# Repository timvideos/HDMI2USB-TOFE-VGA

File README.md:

# VGA TOFE Expansion Board

This repository contains a TOFE board for VGA capture based on 
[Rohit's vmodvga board](https://github.com/timvideos/HDMI2USB-vmodvga).

For [more information on the TOFE interface, see the HDMI2USB website](http://hdmi2usb.tv/tofe).
For the [KiCad website](http://kicad.org/) for more information on using it.

## Parts

The RCA Jack is a little hard to find, but it can be found at the following
locations (it is also totally optional);

 * [Element14](http://au.element14.com/pro-signal/mr-100h/socket-phono-pcb/dp/1267381) - Order Code: 1267381

## License

The contents of this repository excluding "third_party" folder is released
under your choice of the following two licences:

 * the "Creative Commons Attribution-ShareAlike 4.0 International License" (CC
   BY-SA 4.0) full text of this license is included in the LICENSE file and a
   copy can also be found at http://creativecommons.org/licenses/by-sa/4.0/

 * the "TAPR Open Hardware License" full text of this license is included in
   the LICENSE file and a copy can also be found at http://www.tapr.org/OHL

Both these licenses are "share and share alike" licenses and require **any**
derivative work to also be released. Please read the license fully to make sure
you comply with all your obligations.  

## Authors

This board has been a joint effort from many people, some of the major
contributors are;

 * Phyllis McKeever <mccircuit@yahoo.com>
 * Tim 'mithro' Ansell <mithro@mithis.com>
 * Kenny Duffus <kenny@duffus.org>
 * Rohit Kumar Singh <rohit@gmx.it>
 * Jahanzeb Ahmad <jahanzeb1982@gmail.com>

----

Original documentation from vmodvga board.

## Documentation

 * [Project blog](https://dreamsxtrinsic.blogspot.com/) for weekly and daily updates
 * [vMod-VGA Code Block Diagram](https://docs.google.com/drawings/d/1-_QcqhuEnqGTb0JCZim7DaP1v0BfKb7fcv-28n1iaC0/edit?usp=sharing)
 * [Code structure explained in this document](https://docs.google.com/document/d/11dfCeLtNUrjcst97REtgqLIln-_pKwHgGT3xKjOamxs/edit?usp=sharing)
 * [vMod-VGA VHDCI Pin Usage](https://docs.google.com/spreadsheets/d/1f-rBfR98f_ZZNIB7GFV79CGSHQNpj47uOU0JDwOJnV8/edit?usp=sharing)
 * [AD9984A Register Settings](https://docs.google.com/spreadsheets/d/1GH8NDtB8ceGhJEVZQujcXdxDPSw_wLqhg_3s436kkSs/edit?usp=sharing) for easier register settings
 * [Code Test points](https://docs.google.com/spreadsheets/d/12sMpliuKs6eSY12Fc8JHHKd0Y-Cz1OmEMRZJ5Vne3Vg/edit?usp=sharing) I compiled during whole project during
 * [Autodetection guidelines](https://docs.google.com/document/d/1ZhDz50rve5UmnmyKynxySLHqfFuOwBPM7pYFoHo9uvs/edit?usp=sharing)
 * [I2C Tools & Debugging](https://docs.google.com/document/d/1rNem5J1_V4QUOei_MHRzZVJfjsTon8fnE3eTlhzsrj8/edit?usp=sharing)
 * [PCB v02 Requirements Doc](https://docs.google.com/document/d/1EVi7m_RxV2RLTFDjguj92tawxPkJdG1kjHW0T4Z_cDw/edit?usp=sharing)

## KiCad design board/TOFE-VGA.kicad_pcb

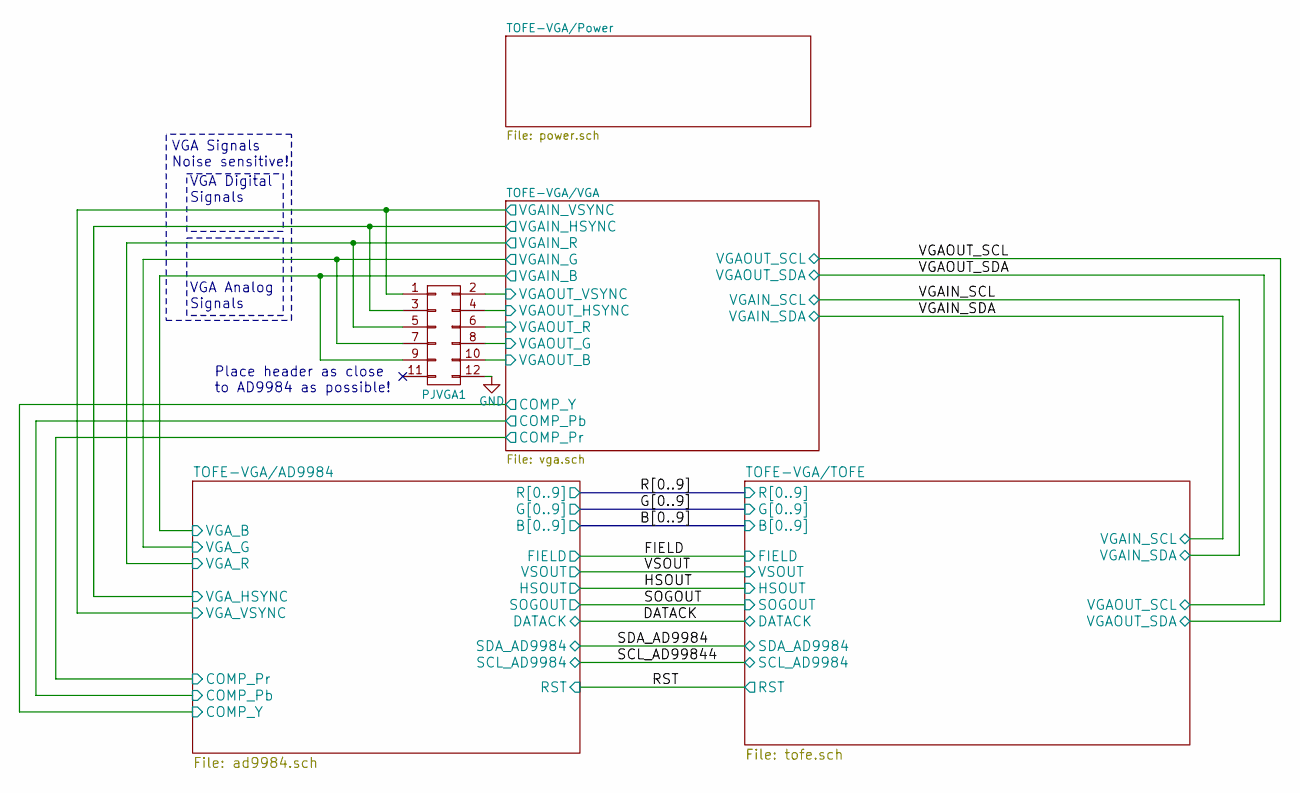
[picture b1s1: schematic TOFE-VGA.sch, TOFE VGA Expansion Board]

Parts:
PJVGA1: CONN_02X06; Pin_Header_Straight_2x06

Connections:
/TOFE-VGA/VGA/VGAIN_B: PJVGA1.9; also elsewhere on the board
/TOFE-VGA/VGA/VGAIN_G: PJVGA1.7; also elsewhere on the board
/TOFE-VGA/VGA/VGAIN_HSYNC: PJVGA1.3; also elsewhere on the board
/TOFE-VGA/VGA/VGAIN_R: PJVGA1.5; also elsewhere on the board
/TOFE-VGA/VGA/VGAIN_VSYNC: PJVGA1.1; also elsewhere on the board
/TOFE-VGA/VGA/VGAOUT_B: PJVGA1.10; also elsewhere on the board
/TOFE-VGA/VGA/VGAOUT_G: PJVGA1.8; also elsewhere on the board
/TOFE-VGA/VGA/VGAOUT_HSYNC: PJVGA1.4; also elsewhere on the board
/TOFE-VGA/VGA/VGAOUT_R: PJVGA1.6; also elsewhere on the board
/TOFE-VGA/VGA/VGAOUT_VSYNC: PJVGA1.2; also elsewhere on the board
GND: PJVGA1.12; also elsewhere on the board

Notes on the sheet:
VGA Signals Noise sensitive!
VGA Analog Signals
Place header as close to AD9984 as possible!
VGA Digital Signals

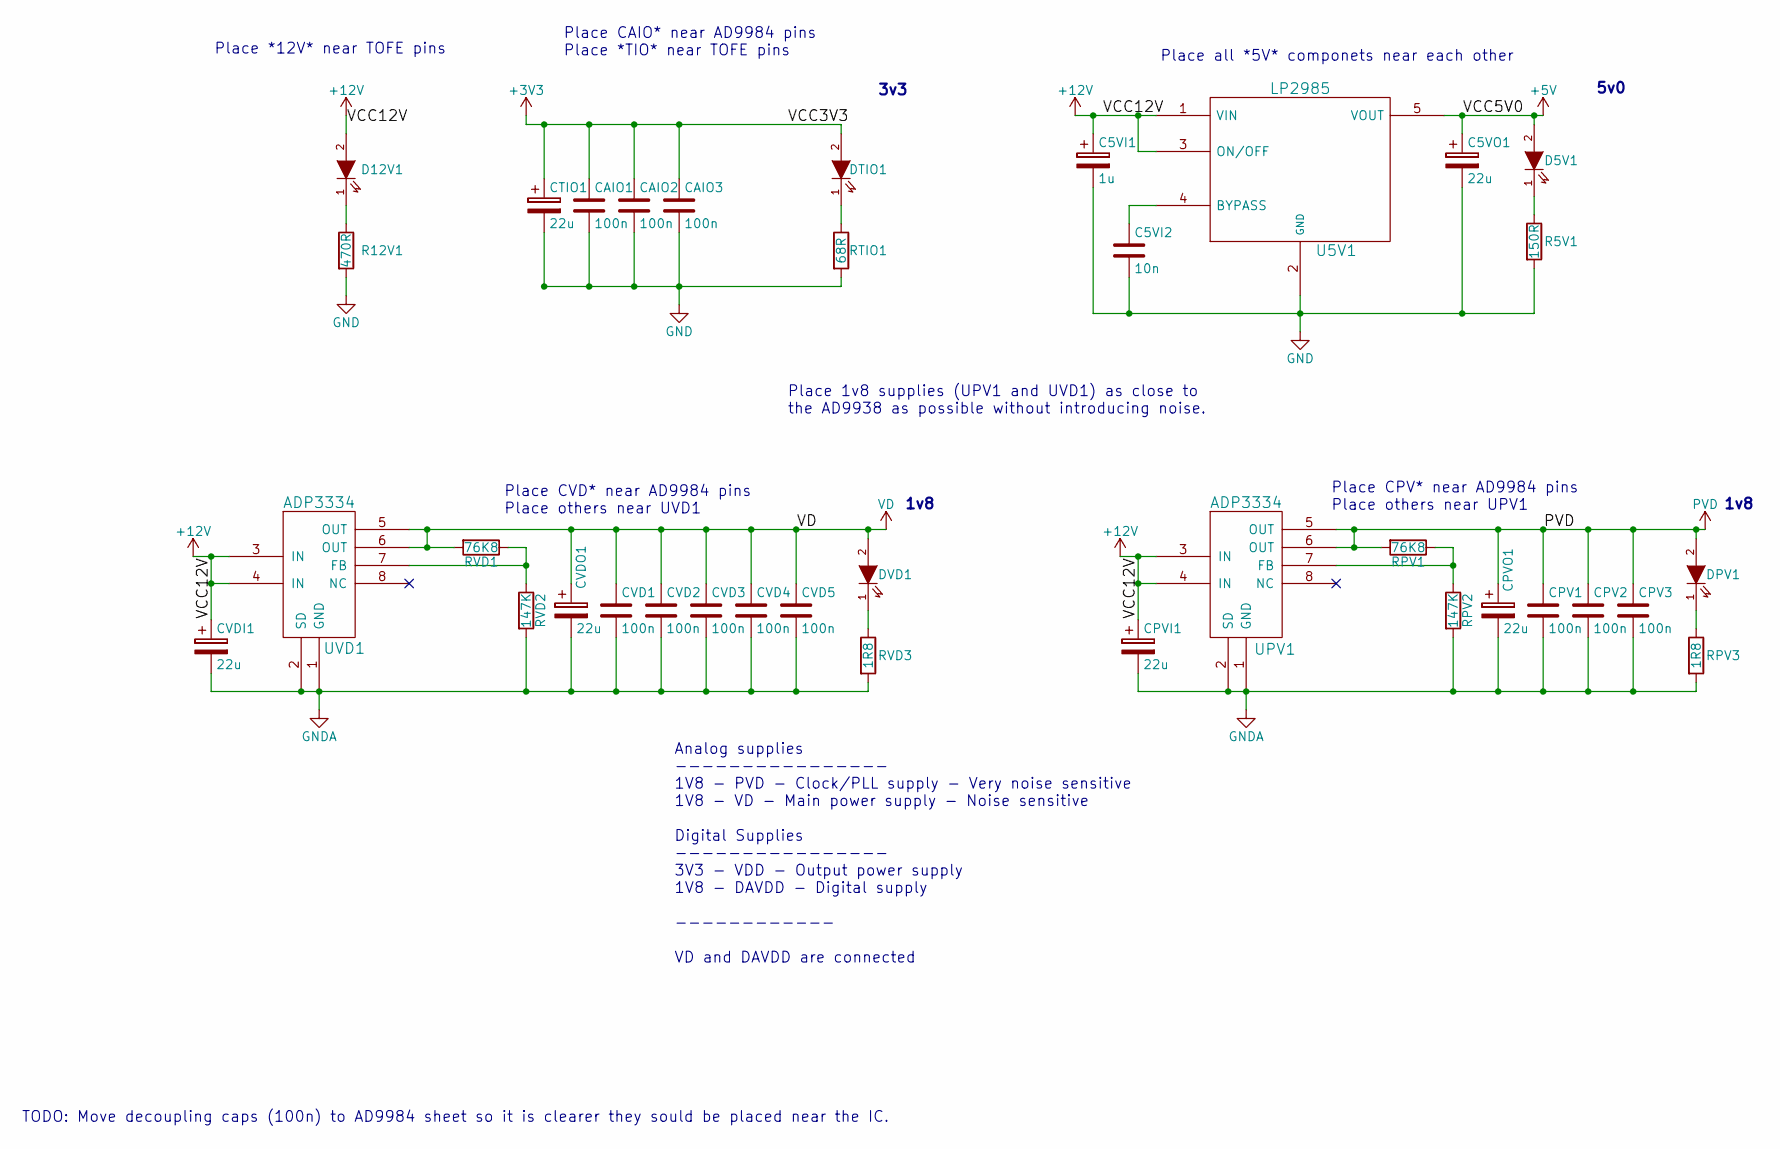
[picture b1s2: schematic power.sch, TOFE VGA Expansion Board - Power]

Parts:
C5VI1: 1u; c_elec_4x5.8
C5VI2: 10n; R_0805_HandSoldering
C5VO1: 22u; c_elec_4x5.8
CAIO1, CAIO2, CAIO3: 100n; R_0805_HandSoldering
CPV1, CPV2, CPV3: 100n; R_0805_HandSoldering
CPVI1: 22u; c_elec_4x5.8
CPVO1: 22u; c_elec_4x5.8
CTIO1: 22u; c_elec_4x5.8
CVD1, CVD2, CVD3, CVD4, CVD5: 100n; R_0805_HandSoldering
CVDI1: 22u; c_elec_4x5.8
CVDO1: 22u; c_elec_4x5.8
D5V1, D12V1: LED; LED_0805
DPV1: LED; LED_0805
DTIO1: LED; LED_0805
DVD1: LED; LED_0805
R5V1: 150R; R_0805_HandSoldering
R12V1: 470R; R_0805_HandSoldering
RPV1: 76K8; R_0805_HandSoldering
RPV2: 147K; R_0805_HandSoldering
RPV3: 1R8; R_0805_HandSoldering
RTIO1: 68R; R_0805_HandSoldering
RVD1: 76K8; R_0805_HandSoldering
RVD2: 147K; R_0805_HandSoldering
RVD3: 1R8; R_0805_HandSoldering
U5V1: LP2985; SOT-23-5
UPV1: ADP3334; MSOP-8_3x3mm_Pitch0.65mm
UVD1: ADP3334; MSOP-8_3x3mm_Pitch0.65mm

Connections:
+3V3: CAIO1.1, CAIO2.1, CAIO3.1, CTIO1.1, DTIO1.2 (A); also elsewhere on the board
+5V: C5VO1.1, D5V1.2 (A), U5V1.5 (VOUT); also elsewhere on the board
+12V: C5VI1.1, CPVI1.1, CVDI1.1, D12V1.2 (A), U5V1.1 (VIN), U5V1.3 (ON/OFF), UPV1.3 (IN), UPV1.4 (IN), UVD1.3 (IN), UVD1.4 (IN); also elsewhere on the board
GND: C5VI1.2, C5VI2.2, C5VO1.2, CAIO1.2, CAIO2.2, CAIO3.2, CTIO1.2, R5V1.2, R12V1.2, RTIO1.2, U5V1.2 (GND); also elsewhere on the board
GNDA: CPV1.2, CPV2.2, CPV3.2, CPVI1.2, CPVO1.2, CVD1.2, CVD2.2, CVD3.2, CVD4.2, CVD5.2, CVDI1.2, CVDO1.2, RPV2.2, RPV3.2, RVD2.2, RVD3.2, UPV1.1 (GND), UPV1.2 (SD), UVD1.1 (GND), UVD1.2 (SD); also elsewhere on the board
unnamed: C5VI2.1, U5V1.4 (BYPASS)
unnamed: D5V1.1 (K), R5V1.1
unnamed: D12V1.1 (K), R12V1.1
unnamed: DPV1.1 (K), RPV3.1
unnamed: DTIO1.1 (K), RTIO1.1
unnamed: DVD1.1 (K), RVD3.1
unnamed: RPV1.1, RPV2.1, UPV1.7 (FB)
unnamed: RVD1.1, RVD2.1, UVD1.7 (FB)
PVD: CPV1.1, CPV2.1, CPV3.1, CPVO1.1, DPV1.2 (A), RPV1.2, UPV1.5 (OUT), UPV1.6 (OUT); also elsewhere on the board
VD: CVD1.1, CVD2.1, CVD3.1, CVD4.1, CVD5.1, CVDO1.1, DVD1.2 (A), RVD1.2, UVD1.5 (OUT), UVD1.6 (OUT); also elsewhere on the board

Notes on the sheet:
3v3
1v8
5v0
Analog supplies ---------------- 1V8 - PVD - Clock/PLL supply - Very noise sensitive 1V8 - VD - Main power supply - Noise sensitive Digital Supplies ---------------- 3V3 - VDD - Output power supply 1V8 - DAVDD - Digital supply ------------ VD and DAVDD are connected
Place CPV* near AD9984 pins Place others near UPV1
Place CVD* near AD9984 pins Place others near UVD1
Place CAIO* near AD9984 pins Place *TIO* near TOFE pins
Place all *5V* componets near each other
Place *12V* near TOFE pins
TODO: Move decoupling caps (100n) to AD9984 sheet so it is clearer they sould be placed near the IC.
Place 1v8 supplies (UPV1 and UVD1) as close to the AD9938 as possible without introducing noise.

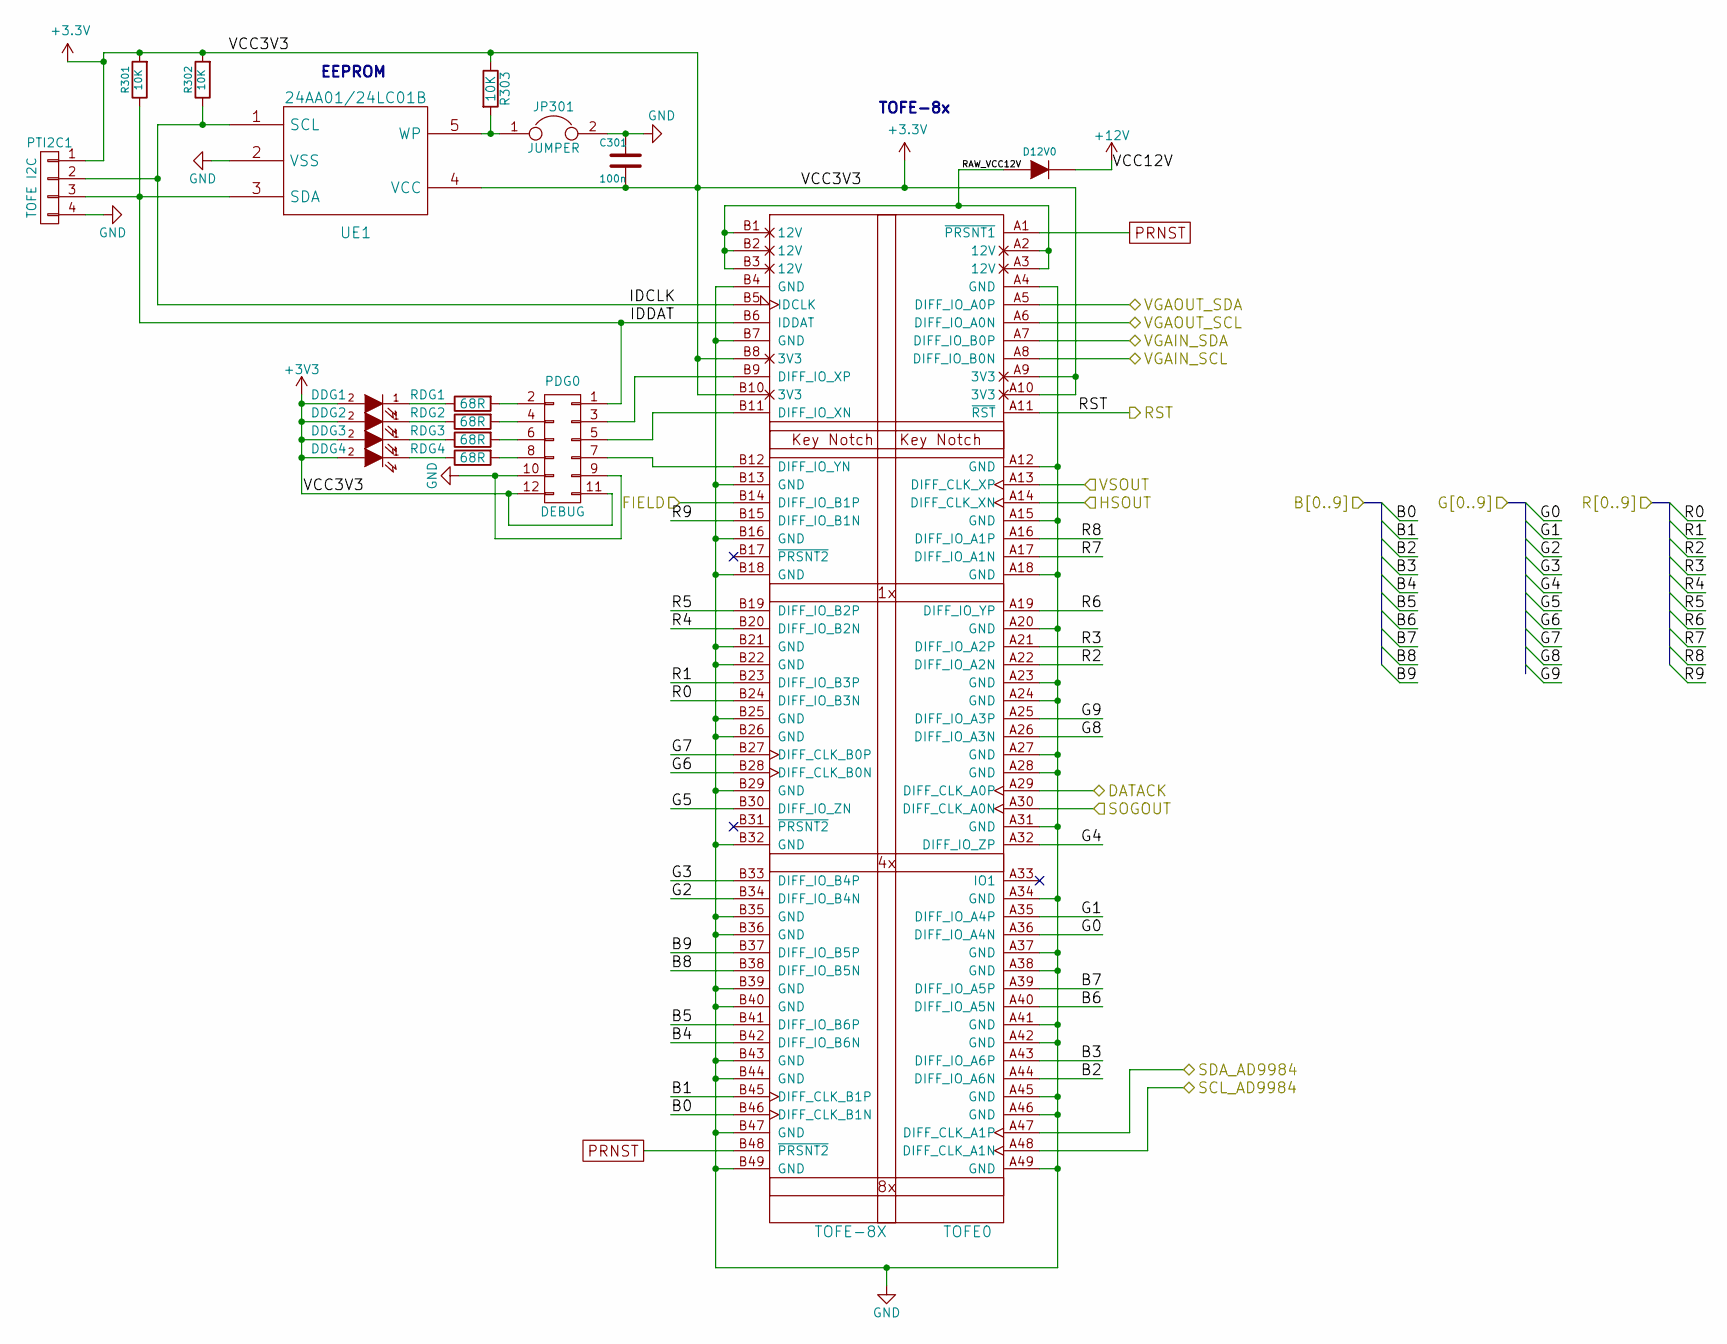
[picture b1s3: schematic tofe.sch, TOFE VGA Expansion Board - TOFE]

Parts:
C301: 100n; C_0805_HandSoldering
D12V0: DIODE; SMB_Handsoldering
DDG1, DDG2, DDG3, DDG4: LED; LED_0805
JP301: JUMPER; HARWIN-M20-87-2x1
PDG0: DEBUG; Pin_Header_Straight_2x06
PTI2C1: TOFE I2C; HARWIN-M20-87-4x1
R301, R302, R303: 10K; R_0603_HandSoldering
RDG1, RDG2, RDG3, RDG4: 68R; R_0603_HandSoldering
TOFE0: TOFE-8X; TOFE_8X_FullHeight
UE1: 24AA01/24LC01B; SOT-23-5

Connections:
+3V3: C301.2, DDG1.2 (A), DDG2.2 (A), DDG3.2 (A), DDG4.2 (A), PDG0.11, PDG0.12, PTI2C1.1, R301.2, R302.2, R303.1, TOFE0.A9 (3V3), TOFE0.A10 (3V3), TOFE0.B8 (3V3), TOFE0.B10 (3V3), UE1.4 (VCC); also elsewhere on the board
+12V: D12V0.2 (K); also elsewhere on the board
/DATACK: TOFE0.A29 (DIFF_CLK_A0P); also elsewhere on the board
/FIELD: TOFE0.B14 (DIFF_IO_B1P); also elsewhere on the board
/HSOUT: TOFE0.A14 (DIFF_CLK_XN); also elsewhere on the board
/RST: TOFE0.A11 (~RST); also elsewhere on the board
/SCL_AD99844: TOFE0.A48 (DIFF_CLK_A1N); also elsewhere on the board
/SDA_AD9984: TOFE0.A47 (DIFF_CLK_A1P); also elsewhere on the board
/SOGOUT: TOFE0.A30 (DIFF_CLK_A0N); also elsewhere on the board
/TOFE-VGA/AD9984/B0: TOFE0.B46 (DIFF_CLK_B1N); also elsewhere on the board
/TOFE-VGA/AD9984/B1: TOFE0.B45 (DIFF_CLK_B1P); also elsewhere on the board
/TOFE-VGA/AD9984/B2: TOFE0.A44 (DIFF_IO_A6N); also elsewhere on the board
/TOFE-VGA/AD9984/B3: TOFE0.A43 (DIFF_IO_A6P); also elsewhere on the board
/TOFE-VGA/AD9984/B4: TOFE0.B42 (DIFF_IO_B6N); also elsewhere on the board
/TOFE-VGA/AD9984/B5: TOFE0.B41 (DIFF_IO_B6P); also elsewhere on the board
/TOFE-VGA/AD9984/B6: TOFE0.A40 (DIFF_IO_A5N); also elsewhere on the board
/TOFE-VGA/AD9984/B7: TOFE0.A39 (DIFF_IO_A5P); also elsewhere on the board
/TOFE-VGA/AD9984/B8: TOFE0.B38 (DIFF_IO_B5N); also elsewhere on the board
/TOFE-VGA/AD9984/B9: TOFE0.B37 (DIFF_IO_B5P); also elsewhere on the board
/TOFE-VGA/AD9984/G0: TOFE0.A36 (DIFF_IO_A4N); also elsewhere on the board
/TOFE-VGA/AD9984/G1: TOFE0.A35 (DIFF_IO_A4P); also elsewhere on the board
/TOFE-VGA/AD9984/G2: TOFE0.B34 (DIFF_IO_B4N); also elsewhere on the board
/TOFE-VGA/AD9984/G3: TOFE0.B33 (DIFF_IO_B4P); also elsewhere on the board
/TOFE-VGA/AD9984/G4: TOFE0.A32 (DIFF_IO_ZP); also elsewhere on the board
/TOFE-VGA/AD9984/G5: TOFE0.B30 (DIFF_IO_ZN); also elsewhere on the board
/TOFE-VGA/AD9984/G6: TOFE0.B28 (DIFF_CLK_B0N); also elsewhere on the board
/TOFE-VGA/AD9984/G7: TOFE0.B27 (DIFF_CLK_B0P); also elsewhere on the board
/TOFE-VGA/AD9984/G8: TOFE0.A26 (DIFF_IO_A3N); also elsewhere on the board
/TOFE-VGA/AD9984/G9: TOFE0.A25 (DIFF_IO_A3P); also elsewhere on the board
/TOFE-VGA/AD9984/R0: TOFE0.B24 (DIFF_IO_B3N); also elsewhere on the board
/TOFE-VGA/AD9984/R1: TOFE0.B23 (DIFF_IO_B3P); also elsewhere on the board
/TOFE-VGA/AD9984/R2: TOFE0.A22 (DIFF_IO_A2N); also elsewhere on the board
/TOFE-VGA/AD9984/R3: TOFE0.A21 (DIFF_IO_A2P); also elsewhere on the board
/TOFE-VGA/AD9984/R4: TOFE0.B20 (DIFF_IO_B2N); also elsewhere on the board
/TOFE-VGA/AD9984/R5: TOFE0.B19 (DIFF_IO_B2P); also elsewhere on the board
/TOFE-VGA/AD9984/R6: TOFE0.A19 (DIFF_IO_YP); also elsewhere on the board
/TOFE-VGA/AD9984/R7: TOFE0.A17 (DIFF_IO_A1N); also elsewhere on the board
/TOFE-VGA/AD9984/R8: TOFE0.A16 (DIFF_IO_A1P); also elsewhere on the board
/TOFE-VGA/AD9984/R9: TOFE0.B15 (DIFF_IO_B1N); also elsewhere on the board
/TOFE-VGA/TOFE/IDCLK: PTI2C1.2, R302.1, TOFE0.B5 (IDCLK), UE1.1 (SCL); also elsewhere on the board
/TOFE-VGA/TOFE/IDDAT: PDG0.1, PTI2C1.3, R301.1, TOFE0.B6 (IDDAT), UE1.3 (SDA); also elsewhere on the board
/TOFE-VGA/TOFE/RAW_VCC12V: D12V0.1 (A), TOFE0.A2 (12V), TOFE0.A3 (12V), TOFE0.B1 (12V), TOFE0.B2 (12V), TOFE0.B3 (12V); also elsewhere on the board
/VGAIN_SCL: TOFE0.A7 (DIFF_IO_B0P); also elsewhere on the board
/VGAIN_SDA: TOFE0.A8 (DIFF_IO_B0N); also elsewhere on the board
/VGAOUT_SCL: TOFE0.A5 (DIFF_IO_A0P); also elsewhere on the board
/VGAOUT_SDA: TOFE0.A6 (DIFF_IO_A0N); also elsewhere on the board
/VSOUT: TOFE0.A13 (DIFF_CLK_XP); also elsewhere on the board
GND: C301.1, JP301.2, PDG0.9, PDG0.10, PTI2C1.4, TOFE0.A4 (GND), TOFE0.A12 (GND), TOFE0.A15 (GND), TOFE0.A18 (GND), TOFE0.A20 (GND), TOFE0.A23 (GND), TOFE0.A24 (GND), TOFE0.A27 (GND), TOFE0.A28 (GND), TOFE0.A31 (GND), TOFE0.A34 (GND), TOFE0.A37 (GND), TOFE0.A38 (GND), TOFE0.A41 (GND), TOFE0.A42 (GND), TOFE0.A45 (GND), TOFE0.A46 (GND), TOFE0.A49 (GND), TOFE0.B4 (GND), TOFE0.B7 (GND), TOFE0.B13 (GND), TOFE0.B16 (GND), TOFE0.B18 (GND), TOFE0.B21 (GND), TOFE0.B22 (GND), TOFE0.B25 (GND), TOFE0.B26 (GND), TOFE0.B29 (GND), TOFE0.B32 (GND), TOFE0.B35 (GND), TOFE0.B36 (GND), TOFE0.B39 (GND), TOFE0.B40 (GND), TOFE0.B43 (GND), TOFE0.B44 (GND), TOFE0.B47 (GND), TOFE0.B49 (GND), UE1.2 (VSS); also elsewhere on the board
unnamed: DDG1.1 (K), RDG1.1
unnamed: DDG2.1 (K), RDG2.1
unnamed: DDG3.1 (K), RDG3.1
unnamed: DDG4.1 (K), RDG4.1
unnamed: JP301.1, R303.2, UE1.5 (WP)
unnamed: PDG0.2, RDG1.2
unnamed: PDG0.3, TOFE0.B9 (DIFF_IO_XP)
unnamed: PDG0.4, RDG2.2
unnamed: PDG0.5, TOFE0.B11 (DIFF_IO_XN)
unnamed: PDG0.6, RDG3.2
unnamed 124: PDG0.7, TOFE0.B12 (DIFF_IO_YN); also elsewhere on the board
unnamed: PDG0.8, RDG4.2
unnamed 139: TOFE0.A33 (IO1); also elsewhere on the board
unnamed 140: TOFE0.B17 (~PRSNT2); also elsewhere on the board
unnamed 141: TOFE0.B31 (~PRSNT2); also elsewhere on the board
PRNST: TOFE0.A1 (~PRSNT1), TOFE0.B48 (~PRSNT2); also elsewhere on the board

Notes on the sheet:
TOFE-8x
EEPROM

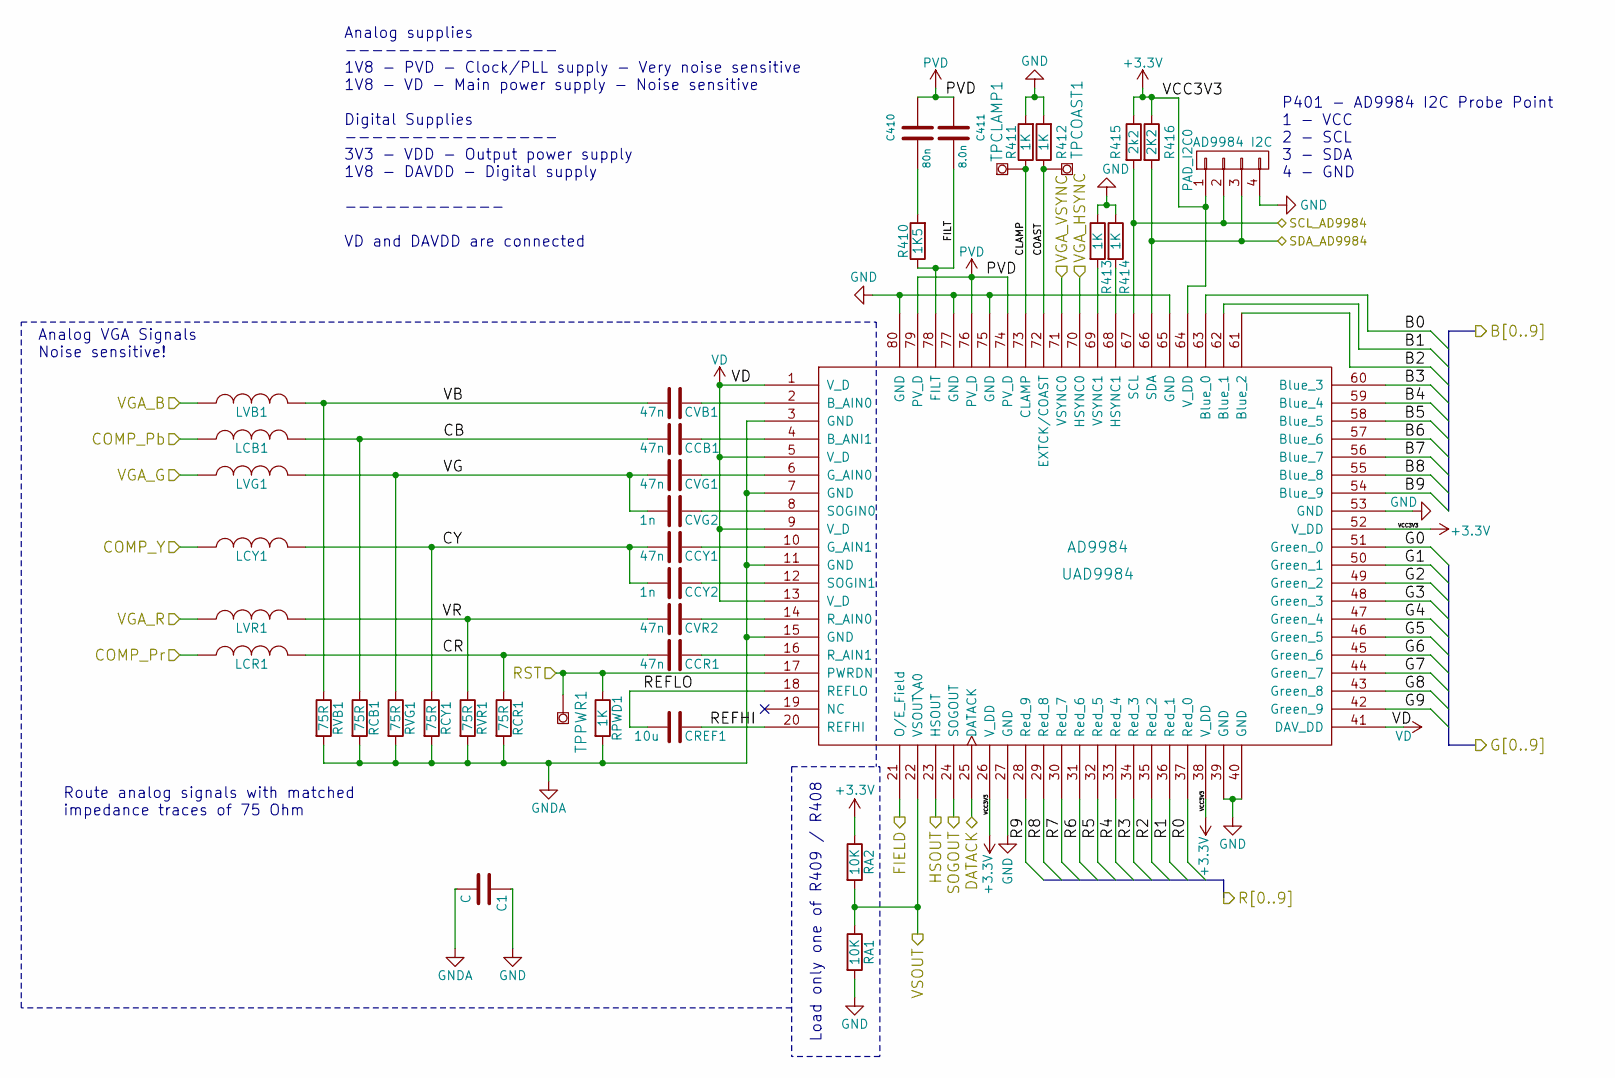
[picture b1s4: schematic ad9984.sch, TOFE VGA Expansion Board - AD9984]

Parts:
C1: C; C_1206_HandSoldering
C410: 80n; R_0805_HandSoldering
C411: 8.0n; R_0805_HandSoldering
CCB1: 47n; R_0805_HandSoldering
CCR1: 47n; R_0805_HandSoldering
CCY1: 47n; R_0805_HandSoldering
CCY2: 1n; R_0805_HandSoldering
CREF1: 10u; R_0805_HandSoldering
CVB1: 47n; R_0805_HandSoldering
CVG1: 47n; R_0805_HandSoldering
CVG2: 1n; R_0805_HandSoldering
CVR2: 47n; R_0805_HandSoldering
LCB1: FERRITE; R_0805_HandSoldering
LCR1: FERRITE; R_0805_HandSoldering
LCY1: FERRITE; R_0805_HandSoldering
LVB1: FERRITE; R_0805_HandSoldering
LVG1: FERRITE; R_0805_HandSoldering
LVR1: FERRITE; R_0805_HandSoldering
PAD_I2C0: AD9984 I2C; HARWIN-M20-87-4x1
R410: 1K5; R_0805_HandSoldering
R411, R412, R413, R414: 1K; R_0805_HandSoldering
R415: 2k2; R_0805_HandSoldering
R416: 2K2; R_0805_HandSoldering
RA1, RA2: 10K; R_0805_HandSoldering
RCB1: 75R; R_0805_HandSoldering
RCR1: 75R; R_0805_HandSoldering
RCY1: 75R; R_0805_HandSoldering
RPWD1: 1K; R_0805_HandSoldering
RVB1: 75R; R_0805_HandSoldering
RVG1: 75R; R_0805_HandSoldering
RVR1: 75R; R_0805_HandSoldering
TPCLAMP1: TESTPOINT; 2MM-TESTPOINT
TPCOAST1: TESTPOINT; 2MM-TESTPOINT
TPPWR1: TESTPOINT; 2MM-TESTPOINT
UAD9984: AD9984; analog-devices2-LQFP80

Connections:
+3V3: PAD_I2C0.1, R415.1, R416.1, RA2.1, UAD9984.26 (V_DD), UAD9984.38 (V_DD), UAD9984.52 (V_DD), UAD9984.64 (V_DD); also elsewhere on the board
/DATACK: UAD9984.25 (DATACK); also elsewhere on the board
/FIELD: UAD9984.21 (O/E_Field); also elsewhere on the board
/HSOUT: UAD9984.23 (HSOUT); also elsewhere on the board
/RST: RPWD1.1, TPPWR1.1, UAD9984.17 (PWRDN); also elsewhere on the board
/SCL_AD99844: PAD_I2C0.2, R415.2, UAD9984.67 (SCL); also elsewhere on the board
/SDA_AD9984: PAD_I2C0.3, R416.2, UAD9984.66 (SDA); also elsewhere on the board
/SOGOUT: UAD9984.24 (SOGOUT); also elsewhere on the board
/TOFE-VGA/AD9984/B0: UAD9984.63 (Blue_0); also elsewhere on the board
/TOFE-VGA/AD9984/B1: UAD9984.62 (Blue_1); also elsewhere on the board
/TOFE-VGA/AD9984/B2: UAD9984.61 (Blue_2); also elsewhere on the board
/TOFE-VGA/AD9984/B3: UAD9984.60 (Blue_3); also elsewhere on the board
/TOFE-VGA/AD9984/B4: UAD9984.59 (Blue_4); also elsewhere on the board
/TOFE-VGA/AD9984/B5: UAD9984.58 (Blue_5); also elsewhere on the board
/TOFE-VGA/AD9984/B6: UAD9984.57 (Blue_6); also elsewhere on the board
/TOFE-VGA/AD9984/B7: UAD9984.56 (Blue_7); also elsewhere on the board
/TOFE-VGA/AD9984/B8: UAD9984.55 (Blue_8); also elsewhere on the board
/TOFE-VGA/AD9984/B9: UAD9984.54 (Blue_9); also elsewhere on the board
/TOFE-VGA/AD9984/CB: CCB1.2, LCB1.2, RCB1.1
/TOFE-VGA/AD9984/CLAMP: R411.1, TPCLAMP1.1, UAD9984.73 (CLAMP)
/TOFE-VGA/AD9984/COAST: R412.1, TPCOAST1.1, UAD9984.72 (EXTCK/COAST)
/TOFE-VGA/AD9984/COMP_Pb: LCB1.1; also elsewhere on the board
/TOFE-VGA/AD9984/COMP_Pr: LCR1.1; also elsewhere on the board
/TOFE-VGA/AD9984/COMP_Y: LCY1.1; also elsewhere on the board
/TOFE-VGA/AD9984/CR: CCR1.2, LCR1.2, RCR1.1
/TOFE-VGA/AD9984/CY: CCY1.2, CCY2.2, LCY1.2, RCY1.1
/TOFE-VGA/AD9984/FILT: C411.2, R410.1, UAD9984.78 (FILT)
/TOFE-VGA/AD9984/G0: UAD9984.51 (Green_0); also elsewhere on the board
/TOFE-VGA/AD9984/G1: UAD9984.50 (Green_1); also elsewhere on the board
/TOFE-VGA/AD9984/G2: UAD9984.49 (Green_2); also elsewhere on the board
/TOFE-VGA/AD9984/G3: UAD9984.48 (Green_3); also elsewhere on the board
/TOFE-VGA/AD9984/G4: UAD9984.47 (Green_4); also elsewhere on the board
/TOFE-VGA/AD9984/G5: UAD9984.46 (Green_5); also elsewhere on the board
/TOFE-VGA/AD9984/G6: UAD9984.45 (Green_6); also elsewhere on the board
/TOFE-VGA/AD9984/G7: UAD9984.44 (Green_7); also elsewhere on the board
/TOFE-VGA/AD9984/G8: UAD9984.43 (Green_8); also elsewhere on the board
/TOFE-VGA/AD9984/G9: UAD9984.42 (Green_9); also elsewhere on the board
/TOFE-VGA/AD9984/R0: UAD9984.37 (Red_0); also elsewhere on the board
/TOFE-VGA/AD9984/R1: UAD9984.36 (Red_1); also elsewhere on the board
/TOFE-VGA/AD9984/R2: UAD9984.35 (Red_2); also elsewhere on the board
/TOFE-VGA/AD9984/R3: UAD9984.34 (Red_3); also elsewhere on the board
/TOFE-VGA/AD9984/R4: UAD9984.33 (Red_4); also elsewhere on the board
/TOFE-VGA/AD9984/R5: UAD9984.32 (Red_5); also elsewhere on the board
/TOFE-VGA/AD9984/R6: UAD9984.31 (Red_6); also elsewhere on the board
/TOFE-VGA/AD9984/R7: UAD9984.30 (Red_7); also elsewhere on the board
/TOFE-VGA/AD9984/R8: UAD9984.29 (Red_8); also elsewhere on the board
/TOFE-VGA/AD9984/R9: UAD9984.28 (Red_9); also elsewhere on the board
/TOFE-VGA/AD9984/REFHI: CREF1.1, UAD9984.20 (REFHI)
/TOFE-VGA/AD9984/REFLO: CREF1.2, UAD9984.18 (REFLO)
/TOFE-VGA/AD9984/VB: CVB1.2, LVB1.2, RVB1.1
/TOFE-VGA/AD9984/VG: CVG1.2, CVG2.2, LVG1.2, RVG1.1
/TOFE-VGA/AD9984/VR: CVR2.2, LVR1.2, RVR1.1
/TOFE-VGA/VGA/VGAIN_B: LVB1.1; also elsewhere on the board
/TOFE-VGA/VGA/VGAIN_G: LVG1.1; also elsewhere on the board
/TOFE-VGA/VGA/VGAIN_HSYNC: UAD9984.70 (HSYNC0); also elsewhere on the board
/TOFE-VGA/VGA/VGAIN_R: LVR1.1; also elsewhere on the board
/TOFE-VGA/VGA/VGAIN_VSYNC: UAD9984.71 (VSYNC0); also elsewhere on the board
/VSOUT: RA1.1, RA2.2, UAD9984.22 (VSOUT\A0); also elsewhere on the board
GND: C1.1, PAD_I2C0.4, R411.2, R412.2, R413.1, R414.1, RA1.2, UAD9984.27 (GND), UAD9984.39 (GND), UAD9984.40 (GND), UAD9984.53 (GND), UAD9984.65 (GND), UAD9984.75 (GND), UAD9984.77 (GND), UAD9984.80 (GND); also elsewhere on the board
GNDA: C1.2, RCB1.2, RCR1.2, RCY1.2, RPWD1.2, RVB1.2, RVG1.2, RVR1.2, UAD9984.3 (GND), UAD9984.7 (GND), UAD9984.11 (GND), UAD9984.15 (GND); also elsewhere on the board
unnamed: C410.2, R410.2
unnamed: CCB1.1, UAD9984.4 (B_ANI1)
unnamed: CCR1.1, UAD9984.16 (R_AIN1)
unnamed: CCY1.1, UAD9984.10 (G_AIN1)
unnamed: CCY2.1, UAD9984.12 (SOGIN1)
unnamed: CVB1.1, UAD9984.2 (B_AIN0)
unnamed: CVG1.1, UAD9984.6 (G_AIN0)
unnamed: CVG2.1, UAD9984.8 (SOGIN0)
unnamed: CVR2.1, UAD9984.14 (R_AIN0)
unnamed: R413.2, UAD9984.69 (VSYNC1)
unnamed: R414.2, UAD9984.68 (HSYNC1)
PVD: C410.1, C411.1, UAD9984.74 (PV_D), UAD9984.76 (PV_D), UAD9984.79 (PV_D); also elsewhere on the board
VD: UAD9984.1 (V_D), UAD9984.5 (V_D), UAD9984.9 (V_D), UAD9984.13 (V_D), UAD9984.41 (DAV_DD); also elsewhere on the board

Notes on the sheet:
Analog supplies ---------------- 1V8 - PVD - Clock/PLL supply - Very noise sensitive 1V8 - VD - Main power supply - Noise sensitive Digital Supplies ---------------- 3V3 - VDD - Output power supply 1V8 - DAVDD - Digital supply ------------ VD and DAVDD are connected
Analog VGA Signals Noise sensitive!
P401 - AD9984 I2C Probe Point 1 - VCC 2 - SCL 3 - SDA 4 - GND
Load only one of R409 / R408
Route analog signals with matched impedance traces of 75 Ohm

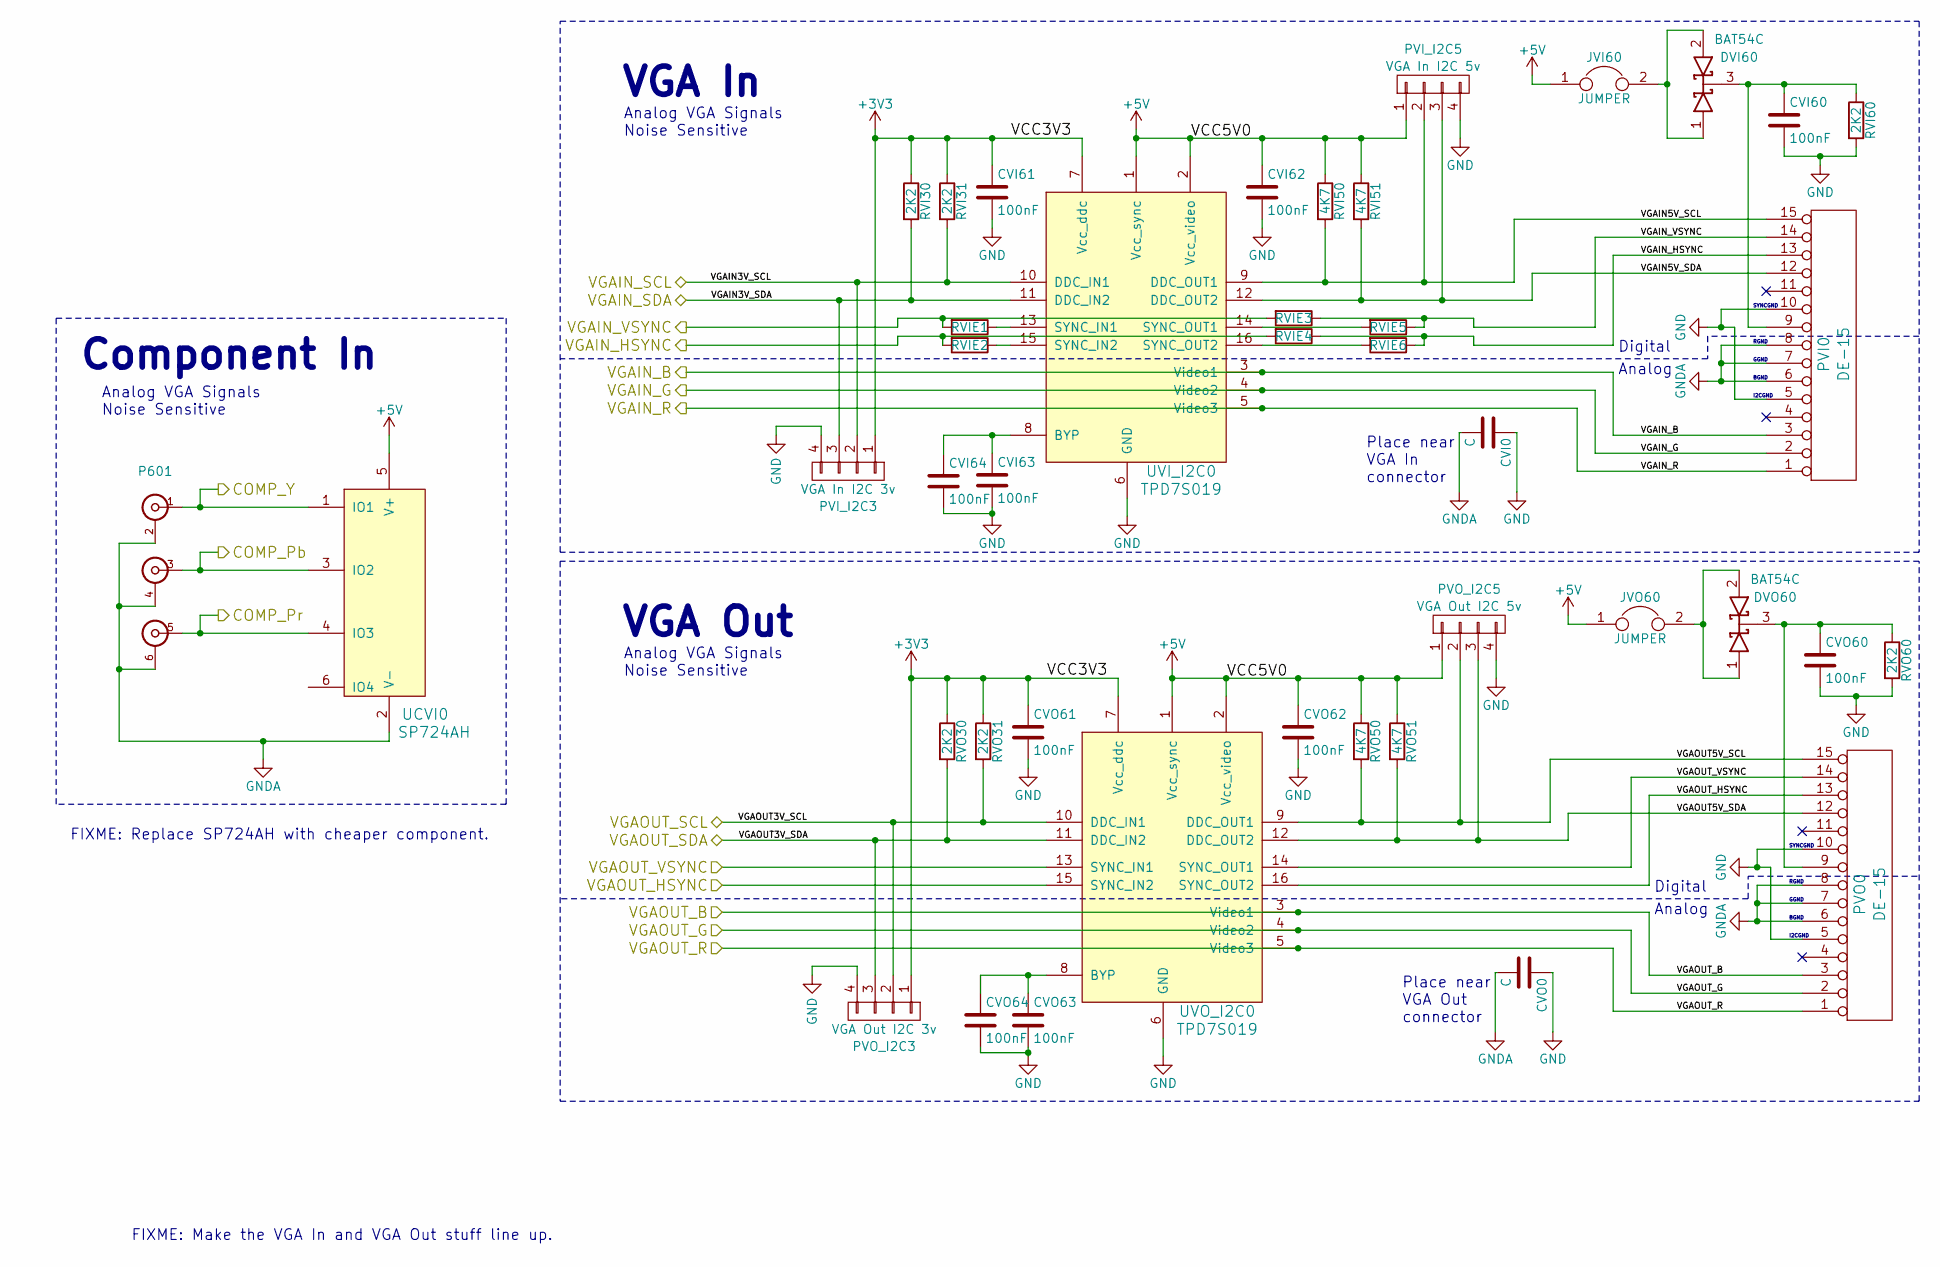
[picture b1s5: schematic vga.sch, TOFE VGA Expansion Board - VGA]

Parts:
CVI0: C; C_1206_HandSoldering
CVI60, CVI61, CVI62, CVI63, CVI64: 100nF; C_1206_HandSoldering
CVO0: C; C_1206_HandSoldering
CVO60, CVO61, CVO62, CVO63, CVO64: 100nF; C_1206_HandSoldering
DVI60: BAT54C; SOT-23
DVO60: BAT54C; SOT-23
JVI60: JUMPER; HARWIN-M20-87-2x1
JVO60: JUMPER; HARWIN-M20-87-2x1
P601: 3-RCA; MR-100H
PVI0: DE-15; TE-1-1734530-1
PVI_I2C3: VGA In I2C 3v; HARWIN-M20-87-4x1
PVI_I2C5: VGA In I2C 5v; HARWIN-M20-87-4x1
PVO0: DE-15; TE-1-1734530-1
PVO_I2C3: VGA Out I2C 3v; HARWIN-M20-87-4x1
PVO_I2C5: VGA Out I2C 5v; HARWIN-M20-87-4x1
RVI30, RVI31, RVI60: 2K2; R_0805_HandSoldering
RVI50, RVI51: 4K7; R_0805_HandSoldering
RVIE1, RVIE2, RVIE3, RVIE4, RVIE5, RVIE6: 0; R_0805_HandSoldering
RVO30, RVO31, RVO60: 2K2; R_0805_HandSoldering
RVO50, RVO51: 4K7; R_0805_HandSoldering
UCVI0: SP724AH; SOT-23-6
UVI_I2C0: TPD7S019; SSOP-16_3.9x4.9mm_Pitch0.635mm
UVO_I2C0: TPD7S019; SSOP-16_3.9x4.9mm_Pitch0.635mm

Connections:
+3V3: CVI61.1, CVO61.1, PVI_I2C3.1, PVO_I2C3.1, RVI30.1, RVI31.1, RVO30.1, RVO31.1, UVI_I2C0.7 (Vcc_ddc), UVO_I2C0.7 (Vcc_ddc); also elsewhere on the board
+5V: CVI62.1, CVO62.1, JVI60.1, JVO60.1, PVI_I2C5.1, PVO_I2C5.1, RVI50.1, RVI51.1, RVO50.1, RVO51.1, UCVI0.5 (V+), UVI_I2C0.1 (Vcc_sync), UVI_I2C0.2 (Vcc_video), UVO_I2C0.1 (Vcc_sync), UVO_I2C0.2 (Vcc_video); also elsewhere on the board
/TOFE-VGA/AD9984/COMP_Pb: P601.3 (In), UCVI0.3 (IO2); also elsewhere on the board
/TOFE-VGA/AD9984/COMP_Pr: P601.5 (In), UCVI0.4 (IO3); also elsewhere on the board
/TOFE-VGA/AD9984/COMP_Y: P601.1 (In), UCVI0.1 (IO1); also elsewhere on the board
/TOFE-VGA/VGA/VGAIN5V_SCL: PVI0.15, PVI_I2C5.2, RVI50.2, UVI_I2C0.9 (DDC_OUT1)
/TOFE-VGA/VGA/VGAIN5V_SDA: PVI0.12, PVI_I2C5.3, RVI51.2, UVI_I2C0.12 (DDC_OUT2)
/TOFE-VGA/VGA/VGAIN_B: PVI0.3, UVI_I2C0.3 (Video1); also elsewhere on the board
/TOFE-VGA/VGA/VGAIN_G: PVI0.2, UVI_I2C0.4 (Video2); also elsewhere on the board
/TOFE-VGA/VGA/VGAIN_HSYNC: PVI0.13, RVIE2.2, RVIE4.1, RVIE4.2, RVIE6.1; also elsewhere on the board
/TOFE-VGA/VGA/VGAIN_R: PVI0.1, UVI_I2C0.5 (Video3); also elsewhere on the board
/TOFE-VGA/VGA/VGAIN_VSYNC: PVI0.14, RVIE1.2, RVIE3.1, RVIE3.2, RVIE5.1; also elsewhere on the board
/TOFE-VGA/VGA/VGAOUT5V_SCL: PVO0.15, PVO_I2C5.2, RVO50.2, UVO_I2C0.9 (DDC_OUT1)
/TOFE-VGA/VGA/VGAOUT5V_SDA: PVO0.12, PVO_I2C5.3, RVO51.2, UVO_I2C0.12 (DDC_OUT2)
/TOFE-VGA/VGA/VGAOUT_B: PVO0.3, UVO_I2C0.3 (Video1); also elsewhere on the board
/TOFE-VGA/VGA/VGAOUT_G: PVO0.2, UVO_I2C0.4 (Video2); also elsewhere on the board
/TOFE-VGA/VGA/VGAOUT_HSYNC: PVO0.13, UVO_I2C0.15 (SYNC_IN2), UVO_I2C0.16 (SYNC_OUT2); also elsewhere on the board
/TOFE-VGA/VGA/VGAOUT_R: PVO0.1, UVO_I2C0.5 (Video3); also elsewhere on the board
/TOFE-VGA/VGA/VGAOUT_VSYNC: PVO0.14, UVO_I2C0.13 (SYNC_IN1), UVO_I2C0.14 (SYNC_OUT1); also elsewhere on the board
/VGAIN_SCL: PVI_I2C3.2, RVI31.2, UVI_I2C0.10 (DDC_IN1); also elsewhere on the board
/VGAIN_SDA: PVI_I2C3.3, RVI30.2, UVI_I2C0.11 (DDC_IN2); also elsewhere on the board
/VGAOUT_SCL: PVO_I2C3.2, RVO31.2, UVO_I2C0.10 (DDC_IN1); also elsewhere on the board
/VGAOUT_SDA: PVO_I2C3.3, RVO30.2, UVO_I2C0.11 (DDC_IN2); also elsewhere on the board
GND: CVI0.1, CVI60.2, CVI61.2, CVI62.2, CVI63.2, CVI64.2, CVO0.1, CVO60.2, CVO61.2, CVO62.2, CVO63.2, CVO64.2, PVI0.5, PVI0.10, PVI_I2C3.4, PVI_I2C5.4, PVO0.5, PVO0.10, PVO_I2C3.4, PVO_I2C5.4, RVI60.2, RVO60.2, UVI_I2C0.6 (GND), UVO_I2C0.6 (GND); also elsewhere on the board
GNDA: CVI0.2, CVO0.2, P601.2 (Ext), P601.4 (Ext), P601.6 (Ext), PVI0.6, PVI0.7, PVI0.8, PVO0.6, PVO0.7, PVO0.8, UCVI0.2 (V-); also elsewhere on the board
unnamed: CVI60.1, DVI60.3 (K), PVI0.9, RVI60.1
unnamed: CVI63.1, CVI64.1, UVI_I2C0.8 (BYP)
unnamed: CVO60.1, DVO60.3 (K), PVO0.9, RVO60.1
unnamed: CVO63.1, CVO64.1, UVO_I2C0.8 (BYP)
unnamed: DVI60.1 (A), DVI60.2 (A), JVI60.2
unnamed: DVO60.1 (A), DVO60.2 (A), JVO60.2
unnamed: RVIE1.1, UVI_I2C0.13 (SYNC_IN1)
unnamed: RVIE2.1, UVI_I2C0.15 (SYNC_IN2)
unnamed: RVIE5.2, UVI_I2C0.14 (SYNC_OUT1)
unnamed: RVIE6.2, UVI_I2C0.16 (SYNC_OUT2)

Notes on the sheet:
VGA Out
Analog VGA Signals Noise Sensitive
Place near VGA Out connector
Component In
VGA In
Place near VGA In connector
FIXME: Make the VGA In and VGA Out stuff line up.
FIXME: Replace SP724AH with cheaper component.
Digital
Analog
RGND
GGND
BGND
SYNCGND
I2CGND

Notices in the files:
ucf/vtc_demo.ucf:
Copyright (c) 2009 Xilinx, Inc.
This design is confidential and proprietary of Xilinx, All Rights Reserved.
board/TOFE-VGA.sch:
License: CC BY SA 4.0 or TAPR
board/vgaExp.kicad_pcb:
(C) Rohit - CC BY-SA 4.0 or TAPR 1.0
